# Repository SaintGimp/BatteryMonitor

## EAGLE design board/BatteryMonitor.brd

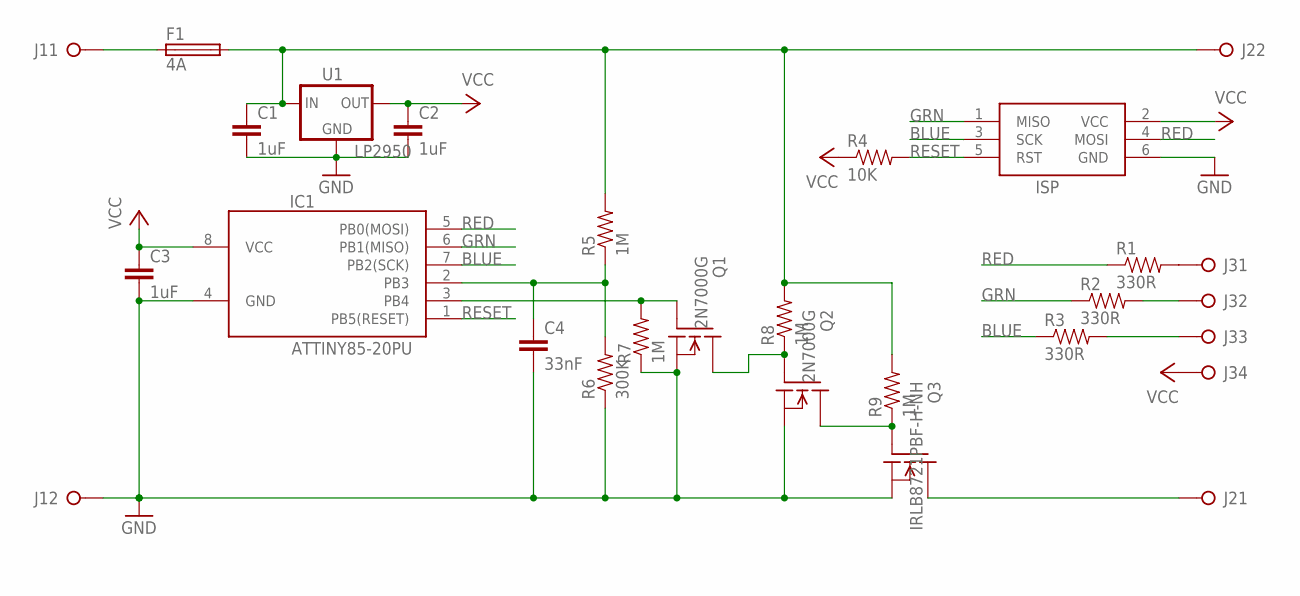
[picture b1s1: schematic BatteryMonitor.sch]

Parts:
C1, C2, C3: 1uF; CAPACITOR-5MM
C4: 33nF; CAPACITOR-5MM
F1: 4A; FUSE_HOLDER_5X20MM
IC1: ATTINY85-20PU; DIP08
ISP: ICSP-HEADER-6; ICSP-HEADER
J1, J2: SCREW-TERM-2
J3: PINHD-1X4; 1X04
Q1, Q2: 2N7000G; TO92-INLINE
Q3: IRLB8721PBF-H-NH; TO220BH-NO-HOLE
R1, R2, R3: 330R; AXIAL-7.5MM
R4: 10K; AXIAL-7.5MM
R5, R7, R8, R9: 1M; AXIAL-7.5MM
R6: 300K; AXIAL-7.5MM
U1: LP2950; TO92-INLINE

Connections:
BAT: C1.1, F1.2, J2.2, R5.P$2 (2), R8.P$2 (2), R9.P$2 (2), U1.3 (IN)
BLUE: IC1.7 (PB2(SCK)), ISP.3 (SCK), R3.P$1 (1)
GND: C1.2, C2.2, C3.2, C4.2, IC1.4 (GND), ISP.6 (GND), J1.2, Q1.1 (SRC), Q2.1 (SRC), Q3.P3 (SRC), R6.P$1 (1), R7.P$1 (1), U1.2 (GND)
GRN: IC1.6 (PB1(MISO)), ISP.1 (MISO), R2.P$1 (1)
unnamed: F1.1, J1.1
unnamed: IC1.3 (PB4), Q1.2 (GATE), R7.P$2 (2)
unnamed: J2.1, Q3.P2 (DRN)
unnamed: C4.1, IC1.2 (PB3), R5.P$1 (1), R6.P$2 (2)
unnamed: Q1.3 (DRN), Q2.2 (GATE), R8.P$1 (1)
unnamed: Q2.3 (DRN), Q3.P1 (GATE), R9.P$1 (1)
unnamed: J3.1, R1.P$2 (2)
unnamed: J3.2, R2.P$2 (2)
unnamed: J3.3, R3.P$2 (2)
RED: IC1.5 (PB0(MOSI)), ISP.4 (MOSI), R1.P$1 (1)
RESET: IC1.1 (PB5(RESET)), ISP.5 (RST), R4.P$2 (2)
VCC: C2.1, C3.1, IC1.8 (VCC), ISP.2 (VCC), J3.4, R4.P$1 (1), U1.1 (OUT)

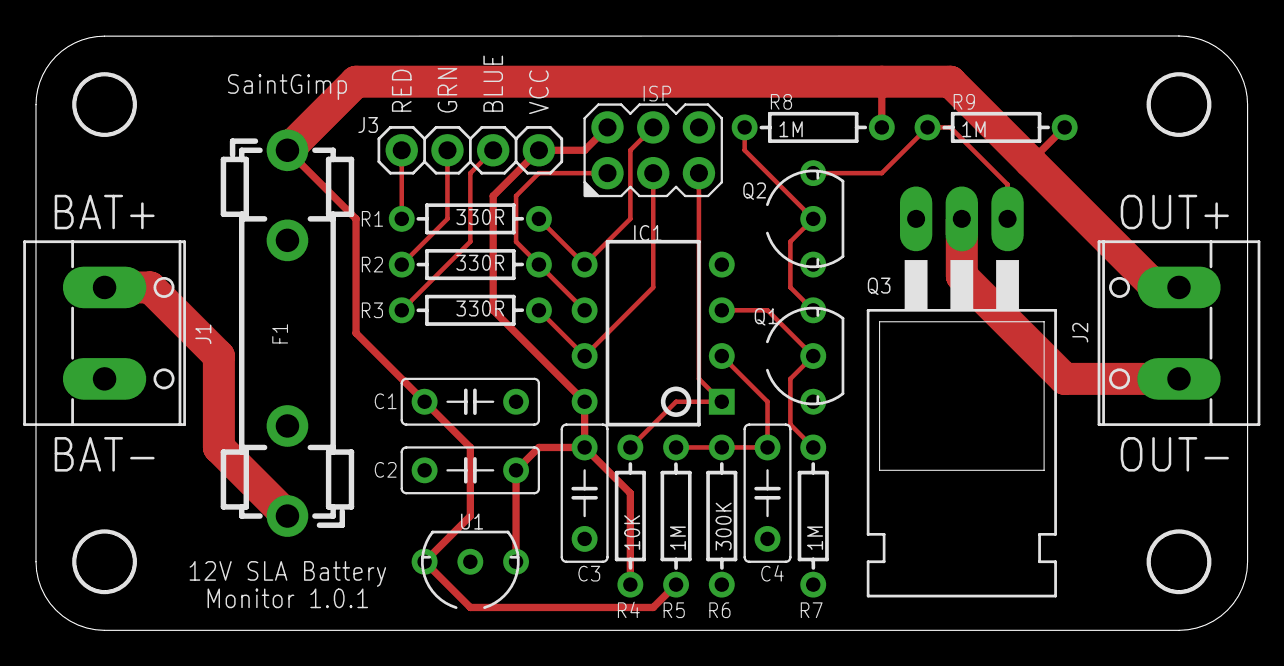
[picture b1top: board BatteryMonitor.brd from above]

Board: 2 copper layers, 67.3 x 33.0 mm, 27 parts (0 on the bottom side), 16 nets.

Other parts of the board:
U$1, U$2, U$3, U$4: MOUNTING-HOLE-3.2MM

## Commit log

2017-03-04 Module that monitors SLA battery charge level and cuts the supply if the charge gets too low
2020-10-08 V2 schematic
2020-10-08 Assign footprints and begin board layout
2020-10-25 Finish layout, first spin
2020-11-10 New code
2020-11-15 Updated code
2021-06-22 Average the voltage for more consistent response
